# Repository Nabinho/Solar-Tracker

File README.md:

# Solar-Tracker
Solar Tracker project with Arduino platform.

Project based on [RoboCore's Solar Panel](https://www.robocore.net/fonte/painel-solar-2w) with TEMT600 ambient light sensors. Controlled by Teensy 3.2, Pololu A-Star Micro and Open Log Module. HMI made with LCD 16x2 with I2C interface and M5Stack CardKB.

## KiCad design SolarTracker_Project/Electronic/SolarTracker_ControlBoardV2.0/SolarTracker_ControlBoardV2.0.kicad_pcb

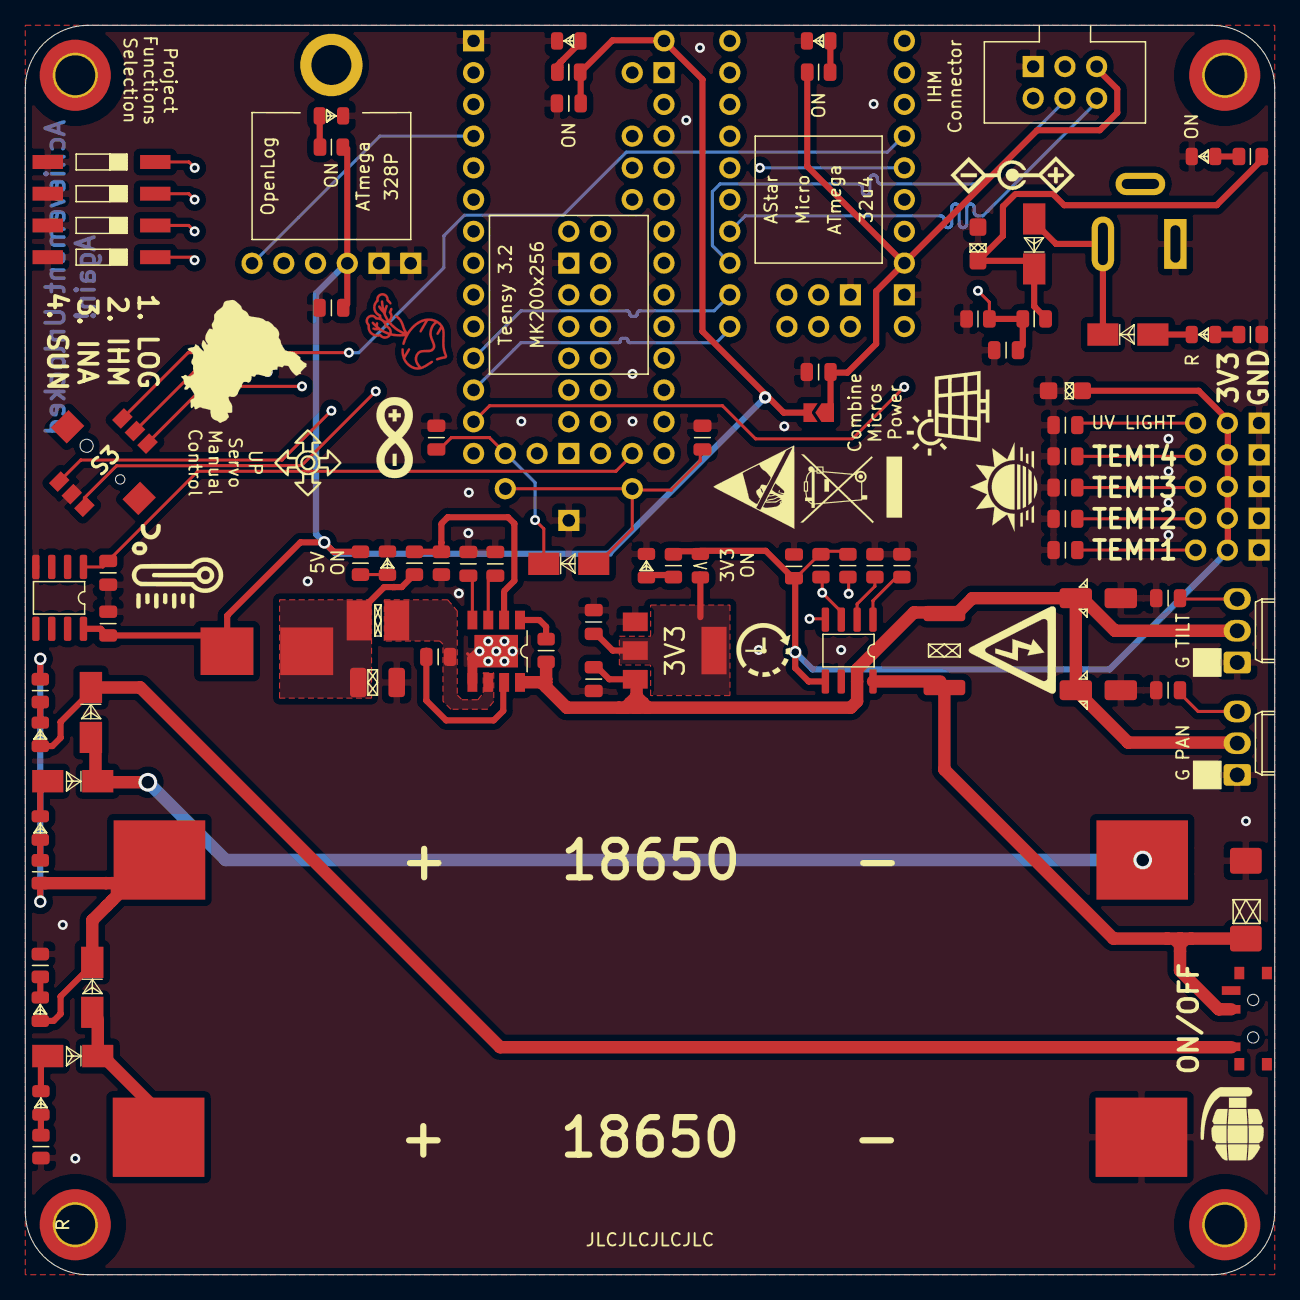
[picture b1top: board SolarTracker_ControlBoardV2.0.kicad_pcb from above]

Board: 4 copper layers, 100.0 x 100.0 mm, 88 parts (0 on the bottom side), 66 nets.

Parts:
BT1, BT2: 18650; BatteryHolder_Keystone_1042_1x18650
BT3: CR2032; CR2032_BatteryHolder_Vertical
C1: 22uF; CP_EIA-7343-31_Kemet-D
C2, C5, C11, C12, C18, C20, C22, C23, C24, C25, C26, C27: 1uF; C_0805_2012Metric
C3, C4: 10uF; CP_Elec_4x5.3
C6, C7, C10, C13, C14, C15, C16, C17, C19: 100nF; C_0805_2012Metric
C8: 47uF; CP_EIA-3528-21_Kemet-B
C9, C21: 10uF; CP_EIA-3216-18_Kemet-A
D1, D4: RED; LED_0805_2012Metric
D2, D5, D12, D18: M7; D_SMA
D3, D6, D13: SS34; D_SMA
D7, D8, D9, D10, D14: B; LED_0805_2012Metric
D11: R; LED_0805_2012Metric
D15, D16, D17: G; LED_0805_2012Metric
F1: Fuse; FUSE_0154004.DR
F2: Fuse; Fuse_0805_2012Metric
J1: Servo_Pan; Molex_KK-254_AE-6410-03A_1x03_P2.54mm_Vertical
J2: Servo_Tilt; Molex_KK-254_AE-6410-03A_1x03_P2.54mm_Vertical
J3: Barrel_Jack_Switch; BarrelJack_Wuerth_6941xx301002
J4: Conn_03x05_Male; PinHeader_3x05_P2.54mm_Vertical
J5: Conn_02x03_Odd_Even; IDC-Header_2x03_P2.54mm_Vertical
JP1: SolderJumper_2_Open; SolderJumper-2_P1.3mm_Open_TrianglePad1.0x1.5mm
L1: 3,3uH; CD32
R1, R2, R3, R4, R10, R14, R15, R25, R26, R27: 1k; R_0805_2012Metric
R5: 100; R_2512_6332Metric
R6, R7, R16: 10k; R_0805_2012Metric
R8, R9: 4k7; R_0805_2012Metric
R11: 100k; R_0805_2012Metric
R12: 124k; R_0805_2012Metric
R13: 22k1; R_0805_2012Metric
R17: 15k; R_0805_2012Metric
R18: 12k; R_0805_2012Metric
S3: SKRHABE010
SW1: SW_SPDT; SW_SPDT_PCM12
SW2: SW_DIP_x04; SW_DIP_SPSTx04_Slide_9.78x12.34mm_W8.61mm_P2.54mm
U1: INA219AxD; SOIC-8_3.9x4.9mm_P1.27mm
U2: AP65552SP-13; Diodes-AP65552SP-13-06_2015-0-0
U3: Teensy3.2; Teensy_3.2
U4: LM35-D; SOIC-8_3.9x4.9mm_P1.27mm
U5: OpenLog
U6: AStar_Micro
U7: AMS1117-3.3; SOT-223-3_TabPin2

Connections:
5V: C22.1, J5.1, JP1.1, R25.1, U6.13
+3V3: C2.1, C21.1, F2.1, J4.1, R8.1, R9.1, R10.2, U1.5
+5V: C12.1, C18.1, C20.2, F1.1, JP1.2, R14.2, R26.1, R27.1, U3.33, U4.8, U5.4
A0: R7.1, U1.2
A1: R6.1, U1.1
AStar_SCL: J5.2, U6.7
AStar_SDA: J5.4, U6.8
A_SolarPanel: C10.1, R17.2, R18.1, U3.28
BS: C7.1, U2.7
BT_A: S3.1, U6.19
BT_B: S3.4, U6.18
BT_C: S3.3, U6.17
BT_D: S3.6, U6.16
BT_M: S3.2, U6.20
DIP1: SW2.1, U3.8
DIP2: SW2.2, U3.7
DIP3: SW2.3, U3.6
DIP4: SW2.4, U3.5
FB: R12.2, R13.1, U2.2
GND: BT1.2, BT3.2, C1.2, C2.2, C3.2, C4.2, C5.2, C6.2, C8.2, C9.2, C10.2, C11.2, C12.2, C13.2, C14.2, C15.2, C16.2, C17.2, C18.2, C19.2, C20.1, C21.2, C22.2, C23.2, C24.2, C25.1, C26.2, C27.2, D9.1, D10.1, D14.1, D15.1, D16.1, D17.1, J1.1, J2.1, J3.2, J4.7, J5.5, R1.2, R3.2, R6.2, R7.2, R13.2, R15.2, R18.2, S3.5, SW2.5, SW2.6, SW2.7, SW2.8, U1.6, U2.5, U2.9, U3.1, U3.17, U3.53, U4.4, U5.5, U5.6, U6.12, U6.21, U7.1
LM35: C19.1, U3.19, U4.1
unnamed: BT1.1, D2.1, D3.2
unnamed: BT2.1, D5.1, D6.2
unnamed: BT3.1, C11.1, D18.2
unnamed: C5.1, U2.3
unnamed: C6.1, U2.4
unnamed: C8.1, F1.2, L1.2, R12.1
unnamed: C24.1, F2.2, U7.2
unnamed: D1.1, D2.2
unnamed: D1.2, R1.1
unnamed: D4.1, D5.2
unnamed: D4.2, R2.1
unnamed: D7.1, R4.1
unnamed: D8.1, R3.1
unnamed: D9.2, R10.1
unnamed: D10.2, R14.1
unnamed: D11.1, D12.2
unnamed: D11.2, R15.1
unnamed: D12.1, D13.2, J3.1
unnamed: D14.2, R16.1
unnamed: D15.2, R25.2
unnamed: D16.2, R26.2
unnamed: D17.2, R27.2
unnamed: R11.2, U2.1
SW: C7.2, L1.1, U2.6
Servo_Pan: C26.1, J1.3, U6.6
Servo_Tilt: C25.2, J2.3, U6.5
TEMT1: C13.1, J4.2, U3.21
TEMT2: C14.1, J4.3, U3.22
TEMT3: C15.1, J4.4, U3.23
TEMT4: C16.1, J4.5, U3.24
Teensy_RX1: U3.2, U5.3
Teensy_RX2: U3.11, U6.9
Teensy_Reset1: U3.4, U5.1
Teensy_Reset2: U3.13, U6.15
Teensy_SCL: R9.2, U1.4, U3.26
Teensy_SDA: R8.2, U1.3, U3.25
Teensy_TX1: U3.3, U5.2
Teensy_TX2: U3.12, U6.10
UV: C17.1, J4.6, U3.27
VBAT1: BT2.2, D3.1, D8.2, R2.2, R4.2
VBAT2: D6.1, D7.2, SW1.1
VBUS: C3.1, C4.1, C23.1, J1.2, J2.2, R5.2, R11.1, U1.7, U2.8, U7.3
VDD: C1.1, R5.1, SW1.2, U1.8
VPP: C9.1, D13.1, R16.2, R17.1
VS: C27.1, D18.1, U3.15

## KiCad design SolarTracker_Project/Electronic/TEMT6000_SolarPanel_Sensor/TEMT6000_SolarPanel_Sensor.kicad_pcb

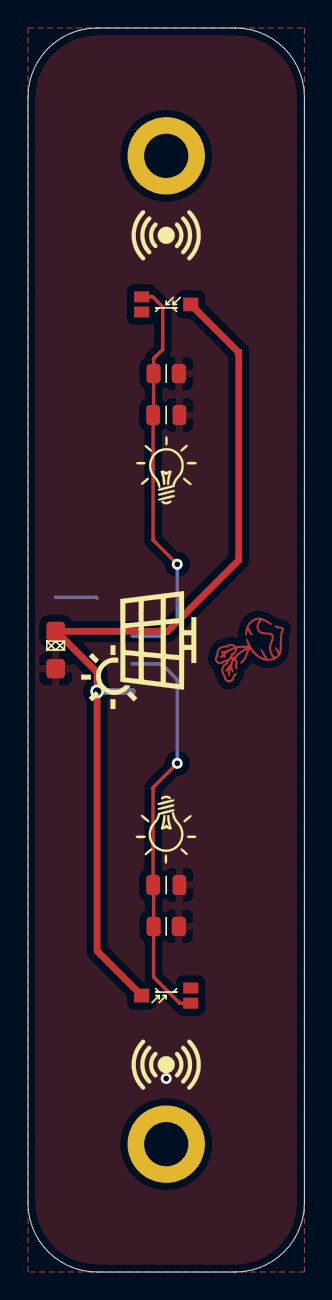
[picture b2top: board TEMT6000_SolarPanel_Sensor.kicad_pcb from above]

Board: 2 copper layers, 20.0 x 90.0 mm, 8 parts (1 on the bottom side), 4 nets.

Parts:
C1: 1uF; CP_EIA-3216-18_Kemet-A
C2, C3: 100nF; C_0805_2012Metric
J1: Conn_01x04; JST_PH_S4B-PH-SM4-TB_1x04-1MP_P2.00mm_Horizontal
Q1, Q2: TEMT6000X01; Vishay_Semiconductors-TEMT6000X01-Manufacturer_Recommended
R1, R2: 10k; R_0805_2012Metric

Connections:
+3V3: C1.1, J1.1, Q1.3, Q2.3
GND: C1.2, C2.2, C3.2, J1.4, R1.2, R2.2
Signal1: C2.1, J1.2, Q1.1, R1.1
Signal2: C3.1, J1.3, Q2.1, R2.1

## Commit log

2022-02-04 Code Update
    Few corrections and library exclusion.
2022-02-09 Software Update
    Servo Easing control, and faster UART communication
